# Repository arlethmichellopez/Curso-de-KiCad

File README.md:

# Curso-de-KiCad
En esta sección integraré el diseño de las PCB's que cree durante el transcurso de mi curso en KiCad

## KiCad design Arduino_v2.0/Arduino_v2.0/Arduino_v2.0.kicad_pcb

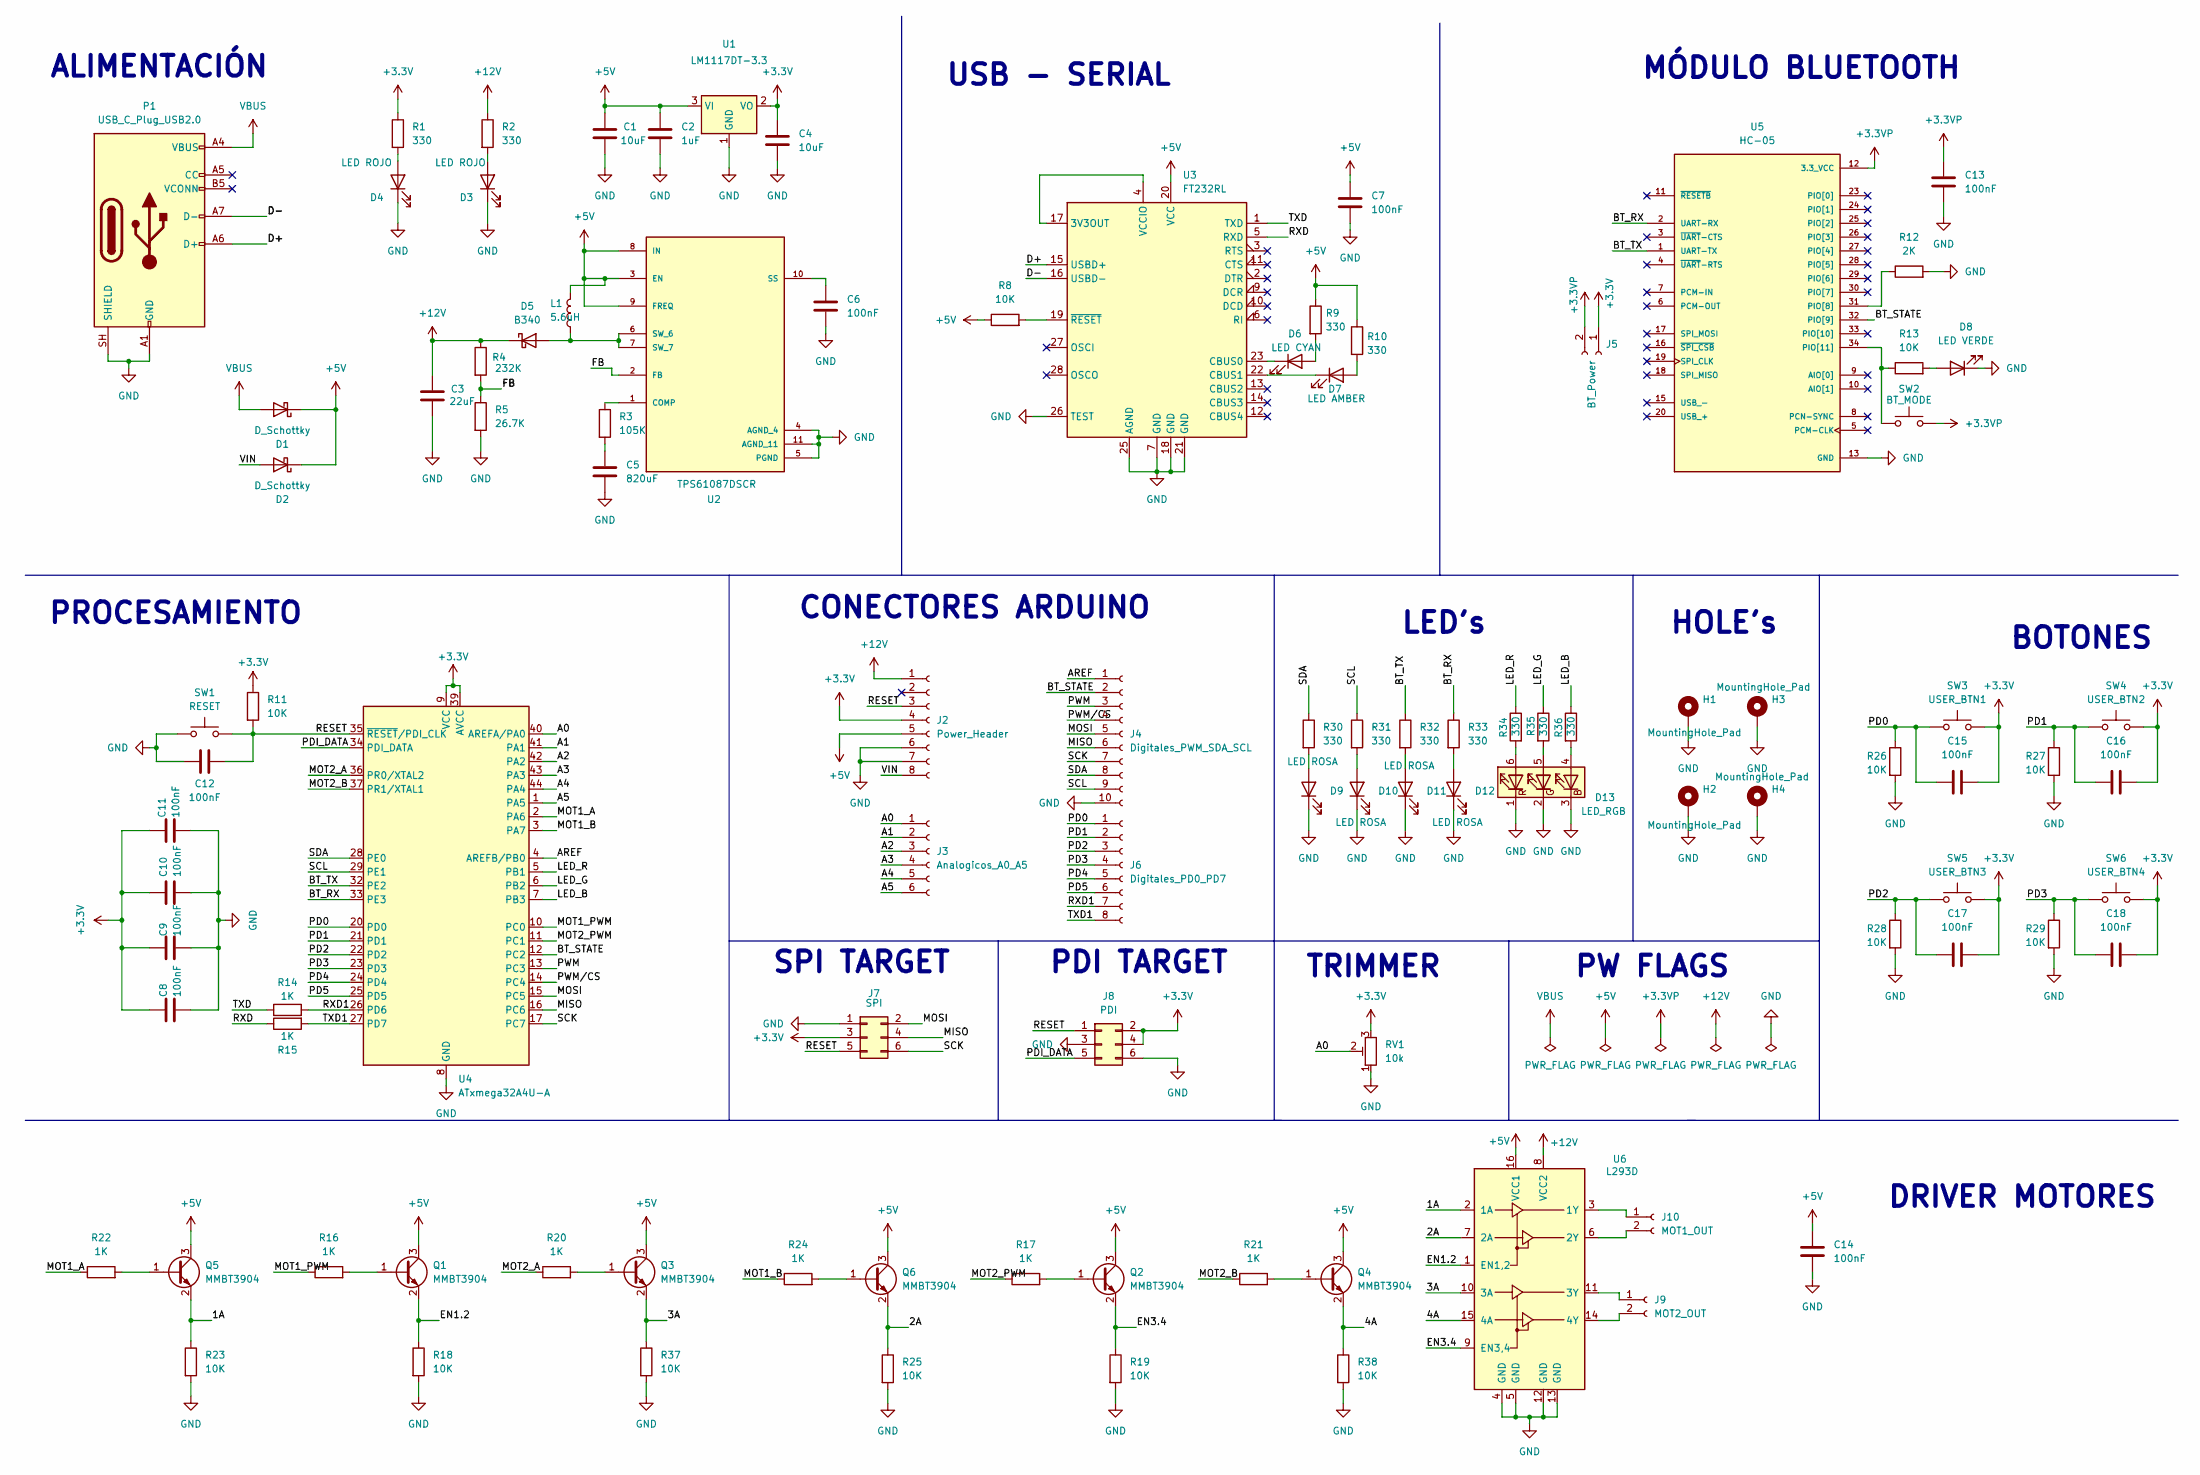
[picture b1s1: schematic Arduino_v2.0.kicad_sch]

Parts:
C1, C4: 10uF; C_0603_1608Metric; LCSC C36911415
C2: 1uF; C_0603_1608Metric; LCSC C95843
C3: 22uF; C_0603_1608Metric; LCSC C29519229
C5: 820uF; C_Elec_10x10.2; LCSC C42393540
C6, C7, C8, C9, C10, C11, C12, C13, C14, C15, C16, C17, C18: 100nF; C_0603_1608Metric; LCSC C92490
D1, D2: D_Schottky; D_SMA; LCSC C8678
D3, D4: LED ROJO; LED_0603_1608Metric; LCSC C19171390
D5: B340; D_SMB; LCSC C6807781
D6: LED CYAN; LED_0603_1608Metric; LCSC C496822
D7: LED AMBER; LED_0603_1608Metric; LCSC C5656657
D8: LED VERDE; LED_0603_1608Metric; LCSC C19273151
D9, D10, D11, D12: LED ROSA; LED_0603_1608Metric; LCSC C51933299
D13: LED_RGB; LED_RGB_5050-6; LCSC C51912161
H1, H2, H3, H4: MountingHole_Pad; MountingHole_3.2mm_M3_DIN965_Pad
J2: Power_Header; PinSocket_1x08_P2.54mm_Vertical; LCSC C42431840
J3: Analogicos_A0_A5; PinSocket_1x06_P2.54mm_Vertical; LCSC C2832269
J4: Digitales_PWM_SDA_SCL; PinSocket_1x10_P2.54mm_Vertical; LCSC C2897373
J5: BT_Power; PinSocket_1x02_P2.54mm_Vertical; LCSC C7499322
J6: Digitales_PD0_PD7; PinSocket_1x08_P2.54mm_Vertical; LCSC C42431840
J7: SPI; PinSocket_2x03_P2.54mm_Vertical; LCSC C541853
J8: PDI; PinSocket_2x03_P2.54mm_Vertical; LCSC C541853
J9: MOT2_OUT; PinSocket_1x02_P2.54mm_Vertical; LCSC C7499322
J10: MOT1_OUT; PinSocket_1x02_P2.54mm_Vertical; LCSC C7499322
L1: 5.6uH; L_7.3x7.3_H3.5; LCSC C475914
P1: USB_C_Plug_USB2.0; C393939; LCSC C42453848
Q1, Q2, Q3, Q4, Q5, Q6: MMBT3904; SOT-23; LCSC C916374
R1, R2, R9, R10, R30, R31, R32, R33, R34, R35, R36: 330; R_0603_1608Metric; LCSC C105881
R3: 105K; R_0603_1608Metric; LCSC C861072
R4: 232K; R_0603_1608Metric; LCSC C861240
R5: 26.7K; R_0603_1608Metric; LCSC C728587
R8, R11, R13, R18, R19, R23, R25, R26, R27, R28, R29, R37, R38: 10K; R_0603_1608Metric; LCSC C98220
R12: 2K; R_0603_1608Metric; LCSC C105576
R14, R15, R16, R17, R20, R21, R22, R24: 1K; R_0603_1608Metric; LCSC C22548
RV1: 10k; Potentiometer_Bourns_3339P_Vertical_HandSoldering
SW1: RESET; SW_SPST_EVQP2_ShortPushTravel_H2.5mm; LCSC C713481
SW2: BT_MODE; SW_SPST_EVQP2_ShortPushTravel_H2.5mm; LCSC C512395
SW3: USER_BTN1; SW_SPST_EVQP2_MiddlePushTravel_H2.5mm; LCSC C713480
SW4: USER_BTN2; SW_SPST_EVQP2_MiddlePushTravel_H2.5mm; LCSC C713480
SW5: USER_BTN3; SW_SPST_EVQP2_MiddlePushTravel_H2.5mm; LCSC C713480
SW6: USER_BTN4; SW_SPST_EVQP2_MiddlePushTravel_H2.5mm; LCSC C713480
U1: LM1117DT-3.3; TO-252-3_TabPin2; LCSC C969102
U2: TPS61087DSCR; IC_TPS61087DSCR; PARTREV A; LCSC C2071336
U3: FT232RL; SSOP-28_5.3x10.2mm_P0.65mm; LCSC C8690
U4: ATxmega32A4U-A; TQFP-44_10x10mm_P0.8mm; LCSC C99821
U5: HC-05; XCVR_HC-05; PARTREV v1.0
U6: L293D; DIP-16_W7.62mm; LCSC C12340

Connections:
+3.3V: C4.1, C8.1, C9.1, C10.1, C11.1, C15.2, C16.2, C17.2, C18.2, J2.4, J5.1, J7.3, J8.2, J8.4, R1.1, R11.1, RV1.3, SW3.2, SW4.2, SW5.2, SW6.2, U1.2 (VO), U4.9 (VCC), U4.19 (VCC), U4.31 (VCC), U4.39 (AVCC)
+3.3VP: C13.1, J5.2, SW2.2, U5.12 (3.3_VCC)
+5V: C1.1, C2.1, C7.1, C14.1, D1.1 (K), D2.1 (K), J2.5, L1.2, Q1.3 (C), Q2.3 (C), Q3.3 (C), Q4.3 (C), Q5.3 (C), Q6.3 (C), R8.1, R9.1, R10.1, U1.3 (VI), U2.3 (EN), U2.8 (IN), U2.9 (FREQ), U3.20 (VCC), U6.16 (VCC1)
+12V: C3.1, D5.1 (K), J2.1, R2.1, R4.1, U6.8 (VCC2)
/1A: Q5.2 (E), R23.1, U6.2 (1A)
/2A: Q6.2 (E), R25.1, U6.7 (2A)
/3A: Q3.2 (E), R37.1, U6.10 (3A)
/4A: Q4.2 (E), R38.1, U6.15 (4A)
/A0: J3.1, RV1.2, U4.40 (AREFA/PA0)
/A1: J3.2, U4.41 (PA1)
/A2: J3.3, U4.42 (PA2)
/A3: J3.4, U4.43 (PA3)
/A4: J3.5, U4.44 (PA4)
/A5: J3.6, U4.1 (PA5)
/AREF: J4.1, U4.4 (AREFB/PB0)
/BT_RX: R33.1, U4.33 (PE3), U5.2 (UART-RX)
/BT_STATE: J4.2, U4.12 (PC2), U5.32 (PIO[9])
/BT_TX: R32.1, U4.32 (PE2), U5.1 (UART-TX)
/D+: P1.A6 (D+), U3.15 (USBD+)
/D-: P1.A7 (D-), U3.16 (USBD-)
/EN1.2: Q1.2 (E), R18.1, U6.1 (EN1,2)
/EN3.4: Q2.2 (E), R19.1, U6.9 (EN3,4)
/FB: R4.2, R5.1, U2.2 (FB)
/LED_B: R36.1, U4.7 (PB3)
/LED_G: R35.1, U4.6 (PB2)
/LED_R: R34.1, U4.5 (PB1)
/MISO: J4.6, J7.4, U4.16 (PC6)
/MOSI: J4.5, J7.2, U4.15 (PC5)
/MOT1_A: R22.1, U4.2 (PA6)
/MOT1_B: R24.1, U4.3 (PA7)
/MOT1_PWM: R16.1, U4.10 (PC0)
/MOT2_A: R20.1, U4.36 (PR0/XTAL2)
/MOT2_B: R21.1, U4.37 (PR1/XTAL1)
/MOT2_PWM: R17.1, U4.11 (PC1)
/PD0: C15.1, J6.1, R26.1, SW3.1, U4.20 (PD0)
/PD1: C16.1, J6.2, R27.1, SW4.1, U4.21 (PD1)
/PD2: C17.1, J6.3, R28.1, SW5.1, U4.22 (PD2)
/PD3: C18.1, J6.4, R29.1, SW6.1, U4.23 (PD3)
/PD4: J6.5, U4.24 (PD4)
/PD5: J6.6, U4.25 (PD5)
/PDI_DATA: J8.5, U4.34 (PDI_DATA)
/PWM: J4.3, U4.13 (PC3)
/PWM/CS: J4.4, U4.14 (PC4)
/RESET: C12.2, J2.3, J7.5, J8.1, R11.2, SW1.2, U4.35 (~RESET/PDI_CLK)
/RXD: R15.1, U3.5 (RXD)
/RXD1: J6.7, R14.2, U4.26 (PD6)
/SCK: J4.7, J7.6, U4.17 (PC7)
/SCL: J4.9, R31.1, U4.29 (PE1)
/SDA: J4.8, R30.1, U4.28 (PE0)
/TXD: R14.1, U3.1 (TXD)
/TXD1: J6.8, R15.2, U4.27 (PD7)
/VIN: D2.2 (A), J2.8
GND: C1.2, C2.2, C3.2, C4.2, C5.2, C6.2, C7.2, C8.2, C9.2, C10.2, C11.2, C12.1, C13.2, C14.2, D3.1 (K), D4.1 (K), D8.1 (K), D9.1 (K), D10.1 (K), D11.1 (K), D12.1 (K), D13.1 (RK), D13.2 (GK), D13.3 (BK), H1.1 (1_1), H2.1 (1_1), H3.1 (1_1), H4.1 (1_1), J2.6, J2.7, J4.10, J7.1, J8.3, J8.6, P1.A1 (GND), P1.A12 (GND), P1.B1 (GND), P1.B12 (GND), P1.SH (SHIELD), R5.2, R12.2, R18.2, R19.2, R23.2, R25.2, R26.2, R27.2, R28.2, R29.2, R37.2, R38.2, RV1.1, SW1.1, U1.1 (GND), U2.4 (AGND_4), U2.5 (PGND), U2.11 (AGND_11), U3.7 (GND), U3.18 (GND), U3.21 (GND), U3.25 (AGND), U3.26 (TEST), U4.8 (GND), U4.18 (GND), U4.30 (GND), U4.38 (GND), U5.13 (GND), U5.21 (GND), U5.22 (GND), U6.4 (GND), U6.5 (GND), U6.12 (GND), U6.13 (GND)
unnamed: C5.1, R3.2
unnamed: D3.2 (A), R2.2
unnamed: D4.2 (A), R1.2
unnamed: D5.2 (A), L1.1, U2.6 (SW_6), U2.7 (SW_7)
unnamed: D6.2 (A), R9.2
unnamed: D6.1 (K), U3.23 (CBUS0)
unnamed: D7.2 (A), R10.2
unnamed: D7.1 (K), U3.22 (CBUS1)
unnamed: D8.2 (A), R13.2
unnamed: D9.2 (A), R30.2
unnamed: D10.2 (A), R31.2
unnamed: D11.2 (A), R32.2
unnamed: D12.2 (A), R33.2
unnamed: D13.4 (BA), R36.2
unnamed: D13.5 (GA), R35.2
unnamed: D13.6 (RA), R34.2
unnamed: J9.1, U6.11 (3Y)
unnamed: J9.2, U6.14 (4Y)
unnamed: J10.1, U6.3 (1Y)
unnamed: J10.2, U6.6 (2Y)
unnamed: Q1.1 (B), R16.2
unnamed: Q2.1 (B), R17.2
unnamed: Q3.1 (B), R20.2
unnamed: Q4.1 (B), R21.2
unnamed: Q5.1 (B), R22.2
unnamed: Q6.1 (B), R24.2
unnamed: R3.1, U2.1 (COMP)
unnamed: C6.1, U2.10 (SS)
unnamed: U3.4 (VCCIO), U3.17 (3V3OUT)
unnamed: R8.2, U3.19 (~RESET)
unnamed: R12.1, U5.31 (PIO[8])
unnamed: R13.1, SW2.1, U5.34 (PIO[11])
VBUS: D1.2 (A), P1.A4 (VBUS), P1.A9 (VBUS), P1.B4 (VBUS), P1.B9 (VBUS)

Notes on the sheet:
TRIMMER
USB - SERIAL
SPI TARGET
MÓDULO BLUETOOTH
DRIVER MOTORES
PDI TARGET
BOTONES
PW FLAGS
HOLE's
ALIMENTACIÓN
CONECTORES ARDUINO
PROCESAMIENTO
LED's

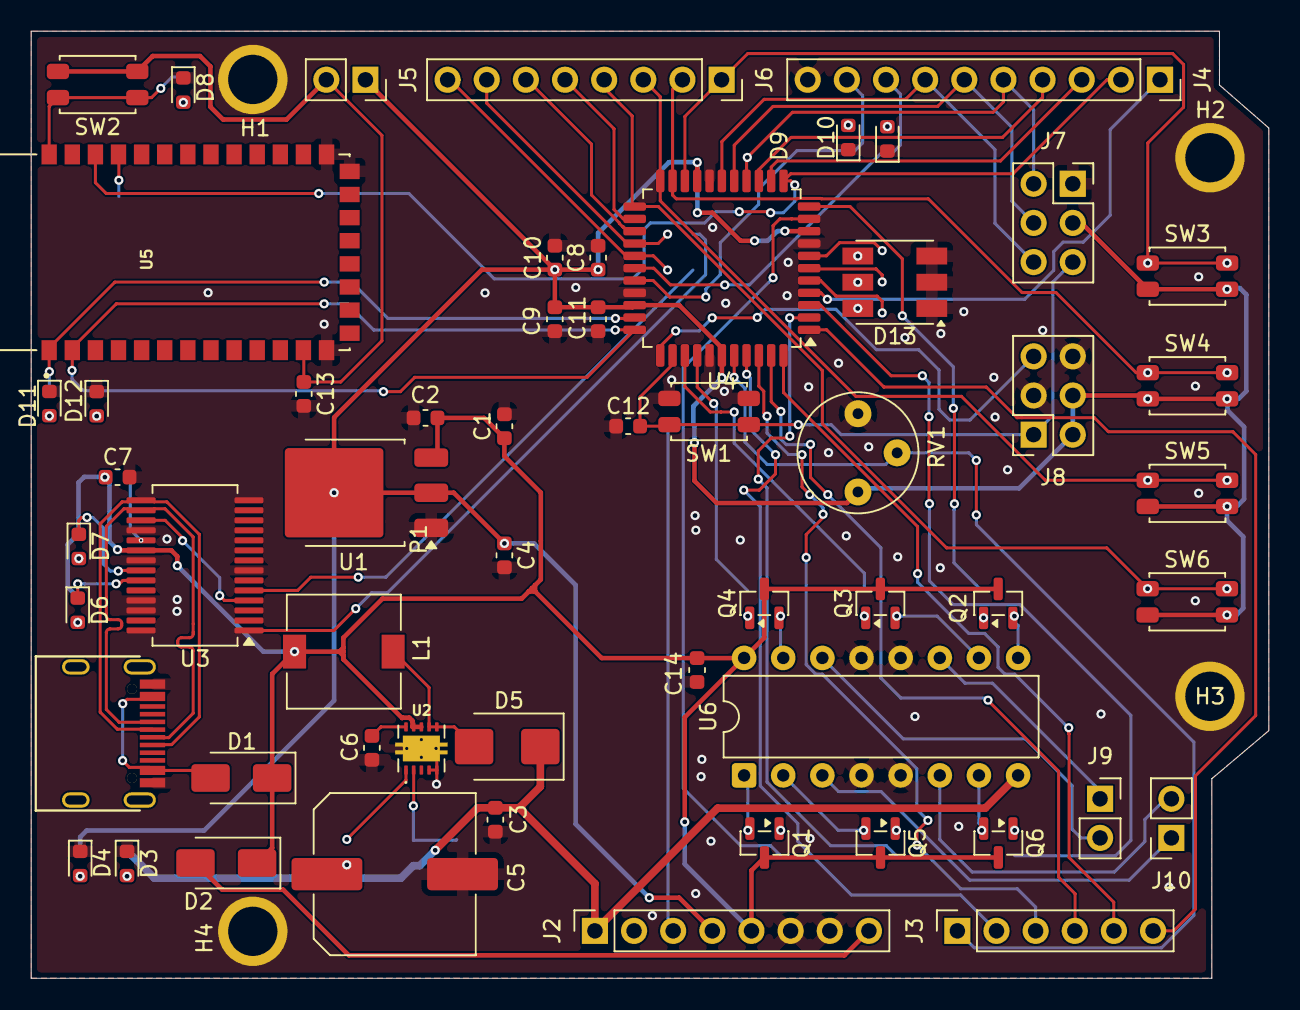
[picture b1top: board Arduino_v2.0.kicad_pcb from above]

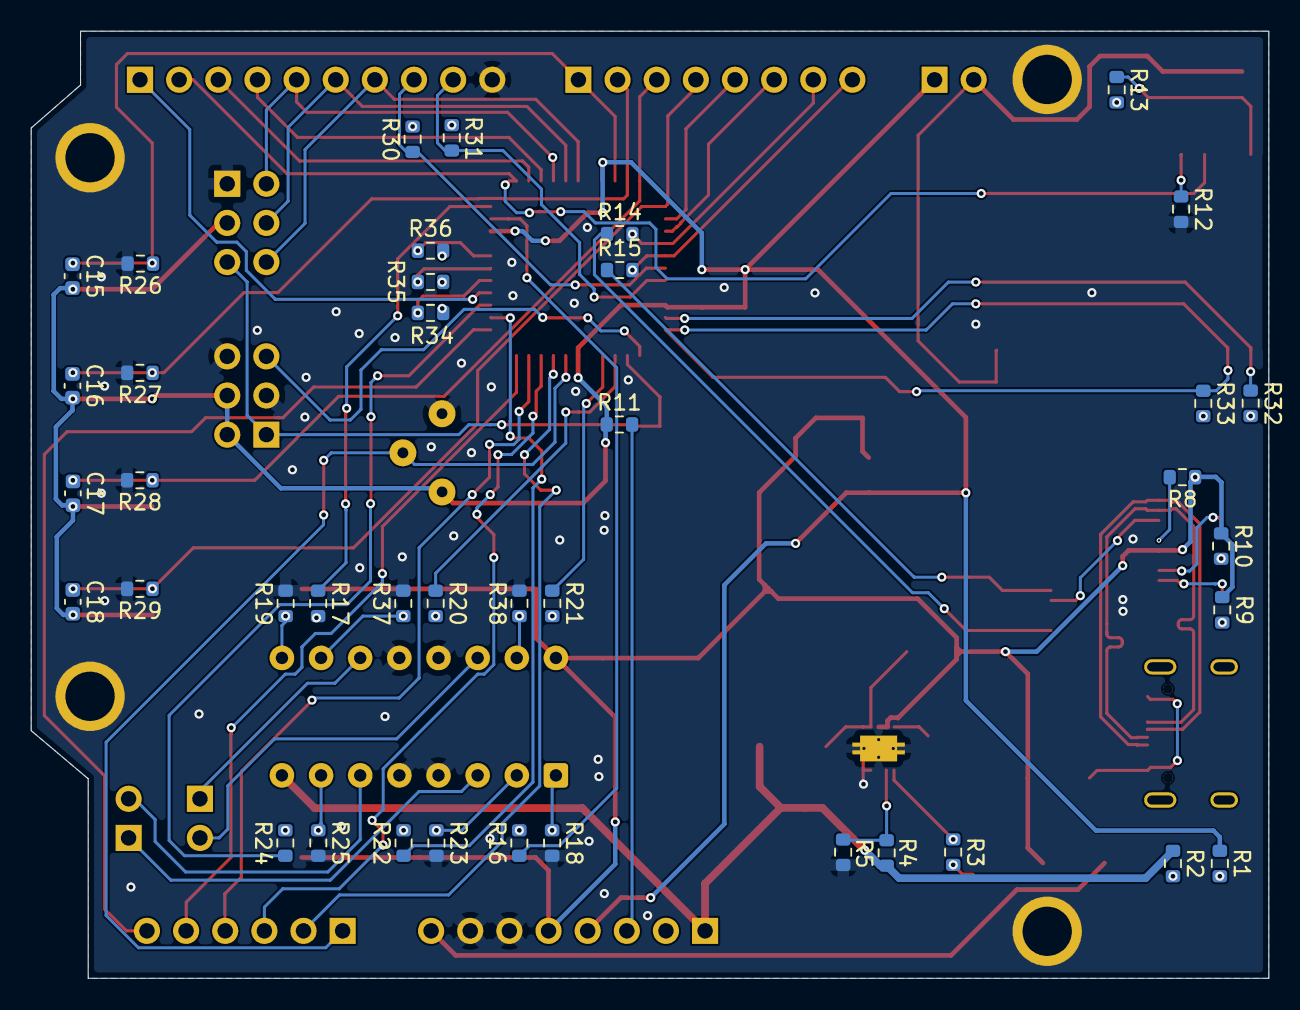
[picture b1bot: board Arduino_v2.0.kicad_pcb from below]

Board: 2 copper layers, 80.3 x 61.5 mm, 101 parts (40 on the bottom side), 86 nets.

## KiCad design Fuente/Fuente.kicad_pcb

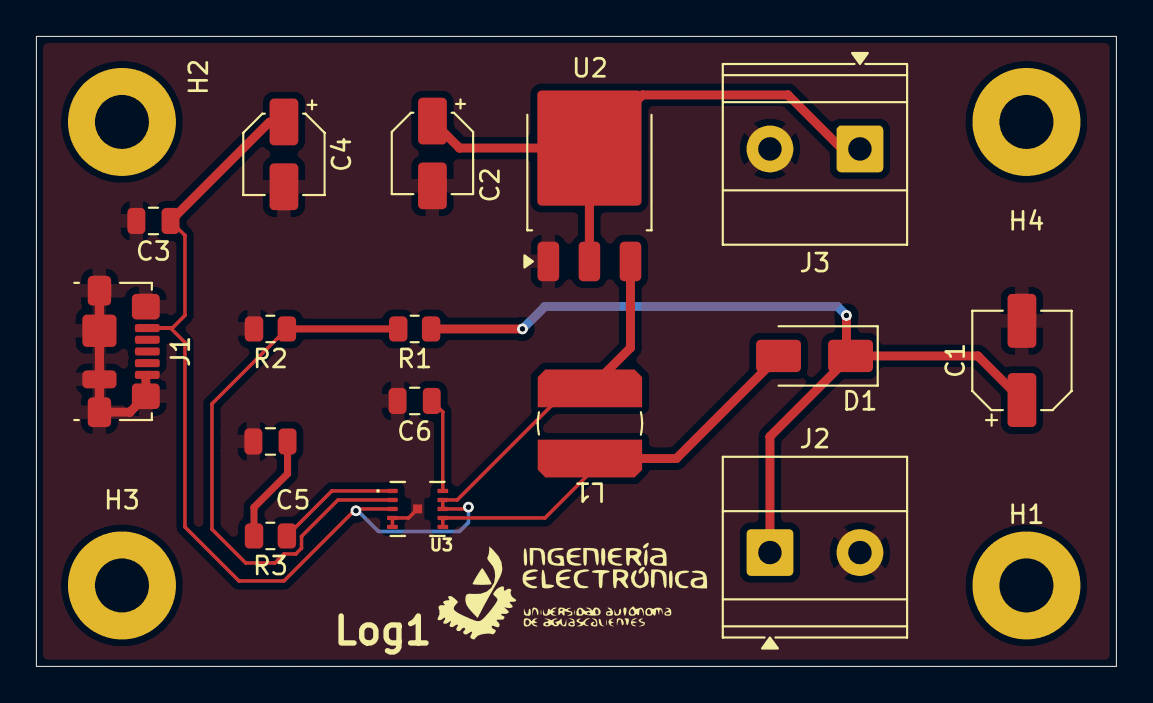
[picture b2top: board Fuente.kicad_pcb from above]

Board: 2 copper layers, 60.0 x 35.0 mm, 21 parts (0 on the bottom side), 9 nets.

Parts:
C1: 22uF; CP_Elec_5x4.5
C2, C4: 10uF; CP_Elec_4x4.5
C3: 1uF; C_0805_2012Metric
C5: 820pF; C_0805_2012Metric
C6: 100nF; C_0805_2012Metric
D1: B340; D_SMA
H1, H2, H3, H4: MountingHole_Pad_MP; MountingHole_3mm_Pad
J1: USB_B_Mini; USB_Micro-B_Molex_47346-0001
J2, J3: Conn_01x02_Pin; TerminalBlock_Phoenix_MKDS-1,5-2_1x02_P5.00mm_Horizontal
L1: SDR0805; L_Bourns_SDR0604
Log1: LOGO; IE UAA
R1: 232k; R_0805_2012Metric
R2: 26.7k; R_0805_2012Metric
R3: 105k; R_0805_2012Metric
U2: LM1117DT-3.3; TO-252-3_TabPin2
U3: TPS61087DSCR; IC_TPS61087DSCR

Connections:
+3.3v: C2.1, J3.1, U2.2 (VO)
+5v: C3.1, C4.1, J1.1 (VBUS), L1.2, U2.3 (VI), U3.3 (EN), U3.8 (IN), U3.9 (FREQ)
+12V: C1.1, D1.1 (K), J2.1, R1.1
/FB: R1.2, R2.1, U3.2 (FB)
GND: C1.2, C2.2, C3.2, C4.2, C5.2, C6.2, J1.5 (GND), J1.SH (Shield), J2.2, J3.2, R2.2, U2.1 (GND), U3.4 (AGND_4), U3.5 (PGND), U3.11 (AGND_11)
unnamed: C5.1, R3.2
unnamed: D1.2 (A), L1.1, U3.6 (SW_6), U3.7 (SW_7)
unnamed: R3.1, U3.1 (COMP)
unnamed: C6.1, U3.10 (SS)
